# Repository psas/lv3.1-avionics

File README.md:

# lv3.1-avionics
Avionics for the LV3.1 rocket

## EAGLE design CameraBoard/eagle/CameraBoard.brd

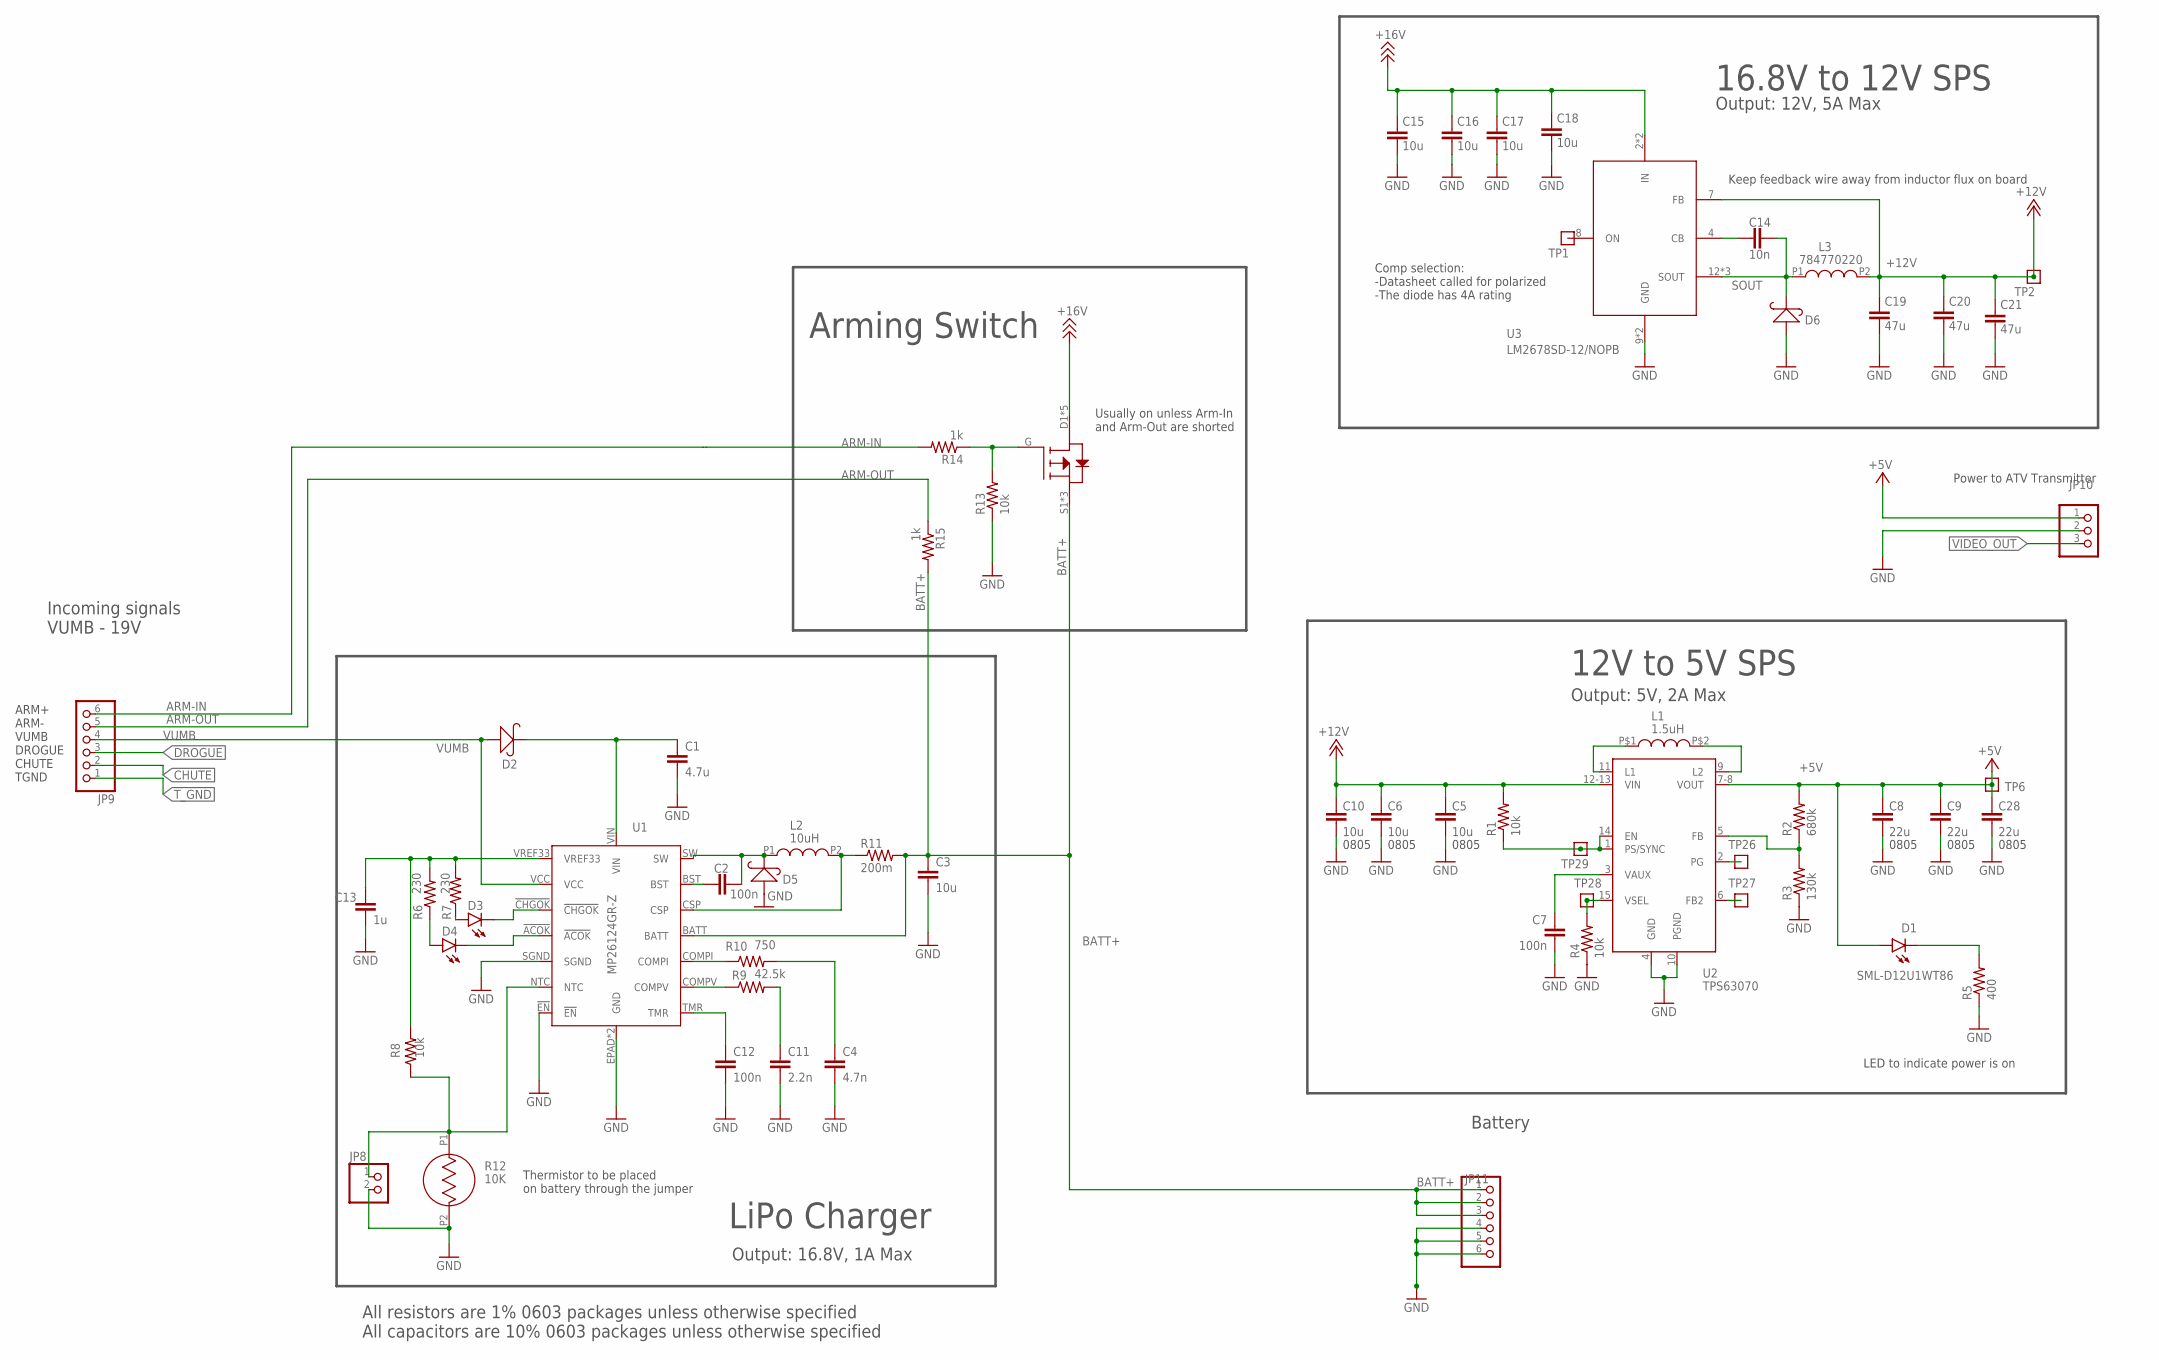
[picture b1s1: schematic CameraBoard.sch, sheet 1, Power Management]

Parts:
C1: 4.7u; .0603-A-NOSILK
C2, C12: 100n; .0603-A-NOSILK
C3: 10u; .0603-A-NOSILK
C4: 4.7n; .0603-A-NOSILK
C5: 10u; .0805-C-NOSILK; MPN CL05B104KO5NNNC
C6, C10: 10u; .0805-C-NOSILK
C7: 100n; .0603-C-NOSILK; MPN CL05B104KO5NNNC
C8: 22u; .0805-C-NOSILK; MPN CL05B104KO5NNNC
C9, C28: 22u; .0805-C-NOSILK
C11: 2.2n; .0603-A-NOSILK
C13: 1u; .0603-A-NOSILK
C14: 10n; .0603-A-NOSILK
C15, C16, C17, C18: 10u; .0805-B-NOSILK
C19, C20, C21: 47u; 1206-A
D1, D3, D4: SML-D12U1WT86; CHIPLED_0603; MPN SML-D12M1WT86
D2, D5: S2MA-13-F
D6: D_MBRS340T3G; SMC
JP8: PINHD-1X2; 1X02
JP9, JP11: PINHD-1X6; 1X06
JP10: PINHD-1X3; 1X03
L1: 1.5uH; IHLP2020CZER1R5M11
L2: 10uH; 1239AS-H-100M=P2
L3: 784770220
Q1: SI7465DP-T1-E3; SI7465DP-T1-E3CT-ND
R1, R4: 10k; .0603-C-NOSILK; MPN RC1005F6653CS
R2: 680k; .0603-C-NOSILK; MPN RC1005F6653CS
R3: 130k; .0603-C-NOSILK; MPN RC1005F6653CS
R5: 400; .0603-C-NOSILK; MPN RC1005F6653CS
R6, R7: 230; .0603-A-NOSILK
R8, R13: 10k; .0603-A-NOSILK
R9: 42.5k; .0603-A-NOSILK
R10: 750; .0603-A-NOSILK
R11: 200m; 1206-A
R12: 10K; NHQ103B375T10
R14, R15: 1k; .0603-A-NOSILK
TP1, TP2, TP6, TP26, TP27, TP28, TP29: TEST-POINT; 2MM-TEST-POINT
U1: MP26124GR-Z
U2: TPS63070; TPS63070X; MPN TPS63070RNMR
U3: LM2678SD-12/NOPB

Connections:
+5V: C8.1, C9.1, C28.1, D1.A, JP10.1, R2.2, TP6.1, U2.7-8 (VOUT); also elsewhere on the board
+12V: C5.1, C6.1, C10.1, C19.1, C20.1, C21.1, L3.P2, R1.2, TP2.1, U2.12-13 (VIN), U3.7 (FB); also elsewhere on the board
+16V: C15.1, C16.1, C17.1, C18.1, Q1.D1 (D), Q1.D2 (D), Q1.D3 (D), Q1.D4 (D), Q1.DPAD (D), U3.2 (IN), U3.3 (IN)
ARM-IN: JP9.6, R14.2
ARM-OUT: JP9.5, R15.1
BATT+: C3.1, JP11.1, JP11.2, JP11.3, Q1.S1 (S), Q1.S2 (S), Q1.S3 (S), R11.2, R15.2, U1.BATT
CHUTE: JP9.2; also elsewhere on the board
DROGUE: JP9.3; also elsewhere on the board
GND: C1.2, C3.2, C4.2, C5.2, C6.2, C7.2, C8.2, C9.2, C10.2, C11.2, C12.2, C13.2, C15.2, C16.2, C17.2, C18.2, C19.2, C20.2, C21.2, C28.2, D5.ANODE (+), D6.2 (+), JP8.2, JP10.2, JP11.4, JP11.5, JP11.6, R3.1, R4.1, R5.1, R12.P2, R13.1, U1.!EN, U1.EPAD (GND), U1.GND, U1.SGND, U2.4 (GND), U2.10 (PGND), U3.9 (GND), U3.DAP (GND); also elsewhere on the board
unnamed: D1.C, R5.2
unnamed: C1.1, D2.CATHODE (-), U1.VIN
unnamed: Q1.G, R13.2, R14.1
unnamed: C13.1, R6.2, R7.2, R8.2, U1.VREF33
unnamed: D4.A, R6.1
unnamed: D3.A, R7.1
unnamed: D3.C, U1.!CHGOK
unnamed: D4.C, U1.!ACOK
unnamed: C12.1, U1.TMR
unnamed: JP8.1, R8.1, R12.P1, U1.NTC
unnamed: R9.1, U1.COMPV
unnamed: C11.1, R9.2
unnamed: R10.1, U1.COMPI
unnamed: C4.1, R10.2
unnamed: C2.1, D5.CATHODE (-), L2.P1, U1.SW
unnamed: C2.2, U1.BST
unnamed: L2.P2, R11.1, U1.CSP
unnamed: TP1.1, U3.8 (ON)
unnamed: C14.2, U3.4 (CB)
SOUT: C14.1, D6.1 (-), L3.P1, U3.12 (SOUT), U3.13 (SOUT), U3.14 (SOUT)
TPS-EN: R1.1, TP29.1, U2.1 (PS/SYNC), U2.14 (EN)
TPS-FB: R2.1, R3.2, U2.5 (FB)
TPS-FB2: TP27.1, U2.6 (FB2)
TPS-L1: L1.P$1, U2.11 (L1)
TPS-L2: L1.P$2, U2.9 (L2)
TPS-PG: TP26.1, U2.2 (PG)
TPS-VAUX: C7.1, U2.3 (VAUX)
TPS-VSEL: R4.2, TP28.1, U2.15 (VSEL)
T_GND: JP9.1; also elsewhere on the board
VIDEO_OUT: JP10.3; also elsewhere on the board
VUMB: D2.ANODE (+), JP9.4, U1.VCC

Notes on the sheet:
Incoming signals VUMB - 19V
Battery
0805
LED to indicate power is on
ARM+ ARM- VUMB DROGUE CHUTE TGND
Usually on unless Arm-In and Arm-Out are shorted
12V to 5V SPS
LiPo Charger
16.8V to 12V SPS
Arming Switch
Power to ATV Transmitter
Keep feedback wire away from inductor flux on board
Comp selection: -Datasheet called for polarized -The diode has 4A rating
Thermistor to be placed on battery through the jumper
All resistors are 1% 0603 packages unless otherwise specified All capacitors are 10% 0603 packages unless otherwise specified
Output: 12V, 5A Max
Output: 5V, 2A Max
Output: 16.8V, 1A Max

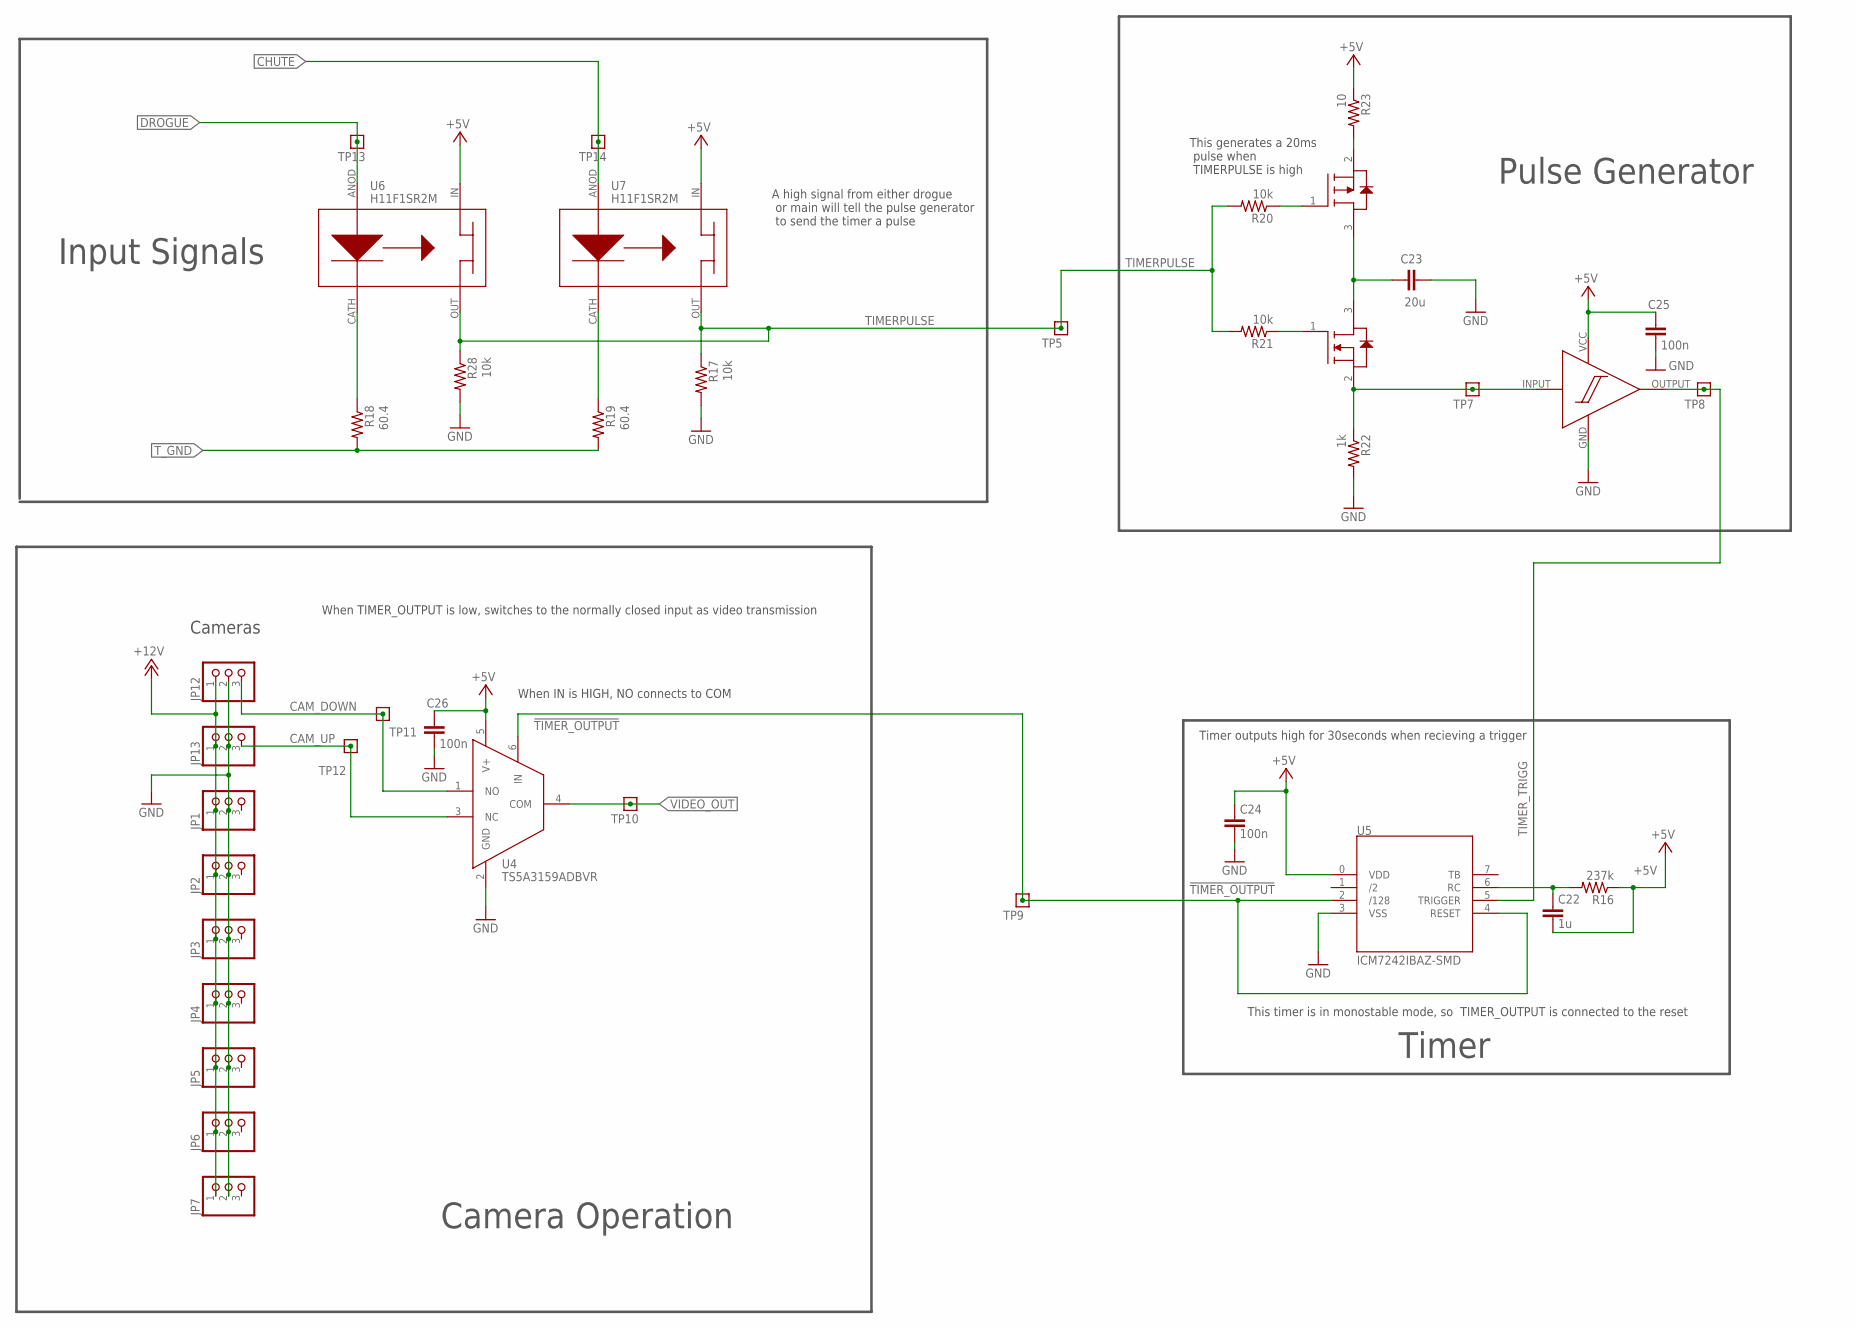
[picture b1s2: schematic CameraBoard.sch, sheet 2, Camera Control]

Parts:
C22: 1u; .0603-C-NOSILK
C23: 20u; .0603-C-NOSILK
C24, C25, C26: 100n; .0603-C-NOSILK
JP1, JP2, JP3, JP4, JP5, JP6, JP7, JP12, JP13: PINHD-1X3; 1X03
Q2: BVSS123LT1G
Q3: BSS84
R16: 237k; .0603-A-NOSILK
R17, R28: 10k; .0603-C-NOSILK
R18, R19: 60.4; .0603-C-NOSILK
R20, R21: 10k; .0603-A-NOSILK
R22: 1k; .0603-A-NOSILK
R23: 10; .0805-A-NOSILK
TP5, TP7, TP8, TP9, TP10, TP11, TP12, TP13, TP14: TEST-POINT; 2MM-TEST-POINT
U4: TS5A3159ADBVR
U5: ICM7242IBAZ-SMD
U6, U7: H11F1SR2M; MPN H11F1SR2M
U8: SN74LVC1G17DCKR

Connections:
!TIMER_OUTPUT: TP9.1, U4.6 (IN), U5.2 (/128), U5.4 (RESET)
+5V: C22.2, C24.1, C25.2, C26.2, R16.1, R23.1, U4.5 (V+), U5.0 (VDD), U6.IN, U7.IN, U8.VCC; also elsewhere on the board
+12V: JP1.1, JP2.1, JP3.1, JP4.1, JP5.1, JP6.1, JP7.1, JP12.1, JP13.1; also elsewhere on the board
CAM_DOWN: JP12.3, TP11.1, U4.1 (NO)
CAM_UP: JP13.3, TP12.1, U4.3 (NC)
CHUTE: TP14.1, U7.ANOD; also elsewhere on the board
DROGUE: TP13.1, U6.ANOD; also elsewhere on the board
GND: C23.2, C24.2, C25.1, C26.1, JP1.2, JP2.2, JP3.2, JP4.2, JP5.2, JP6.2, JP7.2, JP12.2, JP13.2, R17.2, R22.2, R28.2, U4.2 (GND), U5.3 (VSS), U8.GND; also elsewhere on the board
unnamed: R18.1, U6.CATH (CAT)
unnamed: R19.1, U7.CATH (CAT)
unnamed: C22.1, R16.2, U5.6 (RC)
unnamed: C23.1, Q2.3 (D), Q3.3 (D)
unnamed: Q3.2 (S), R23.2
unnamed: Q3.1 (G), R20.1
unnamed: Q2.1 (G), R21.1
SCHMITTIN: Q2.2 (S), R22.1, TP7.1, U8.INPUT (A)
TIMERPULSE: R17.1, R20.2, R21.2, R28.1, TP5.1, U6.OUT, U7.OUT
TIMER_TRIGG: TP8.1, U5.5 (TRIGGER), U8.OUTPUT (Y)
T_GND: R18.2, R19.2; also elsewhere on the board
VIDEO_OUT: TP10.1, U4.4 (COM); also elsewhere on the board

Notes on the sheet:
Cameras
Camera Operation
This timer is in monostable mode, so TIMER_OUTPUT is connected to the reset
A high signal from either drogue or main will tell the pulse generator to send the timer a pulse
Input Signals
Timer
Pulse Generator
This generates a 20ms pulse when TIMERPULSE is high
When TIMER_OUTPUT is low, switches to the normally closed input as video transmission
When IN is HIGH, NO connects to COM
Timer outputs high for 30seconds when recieving a trigger

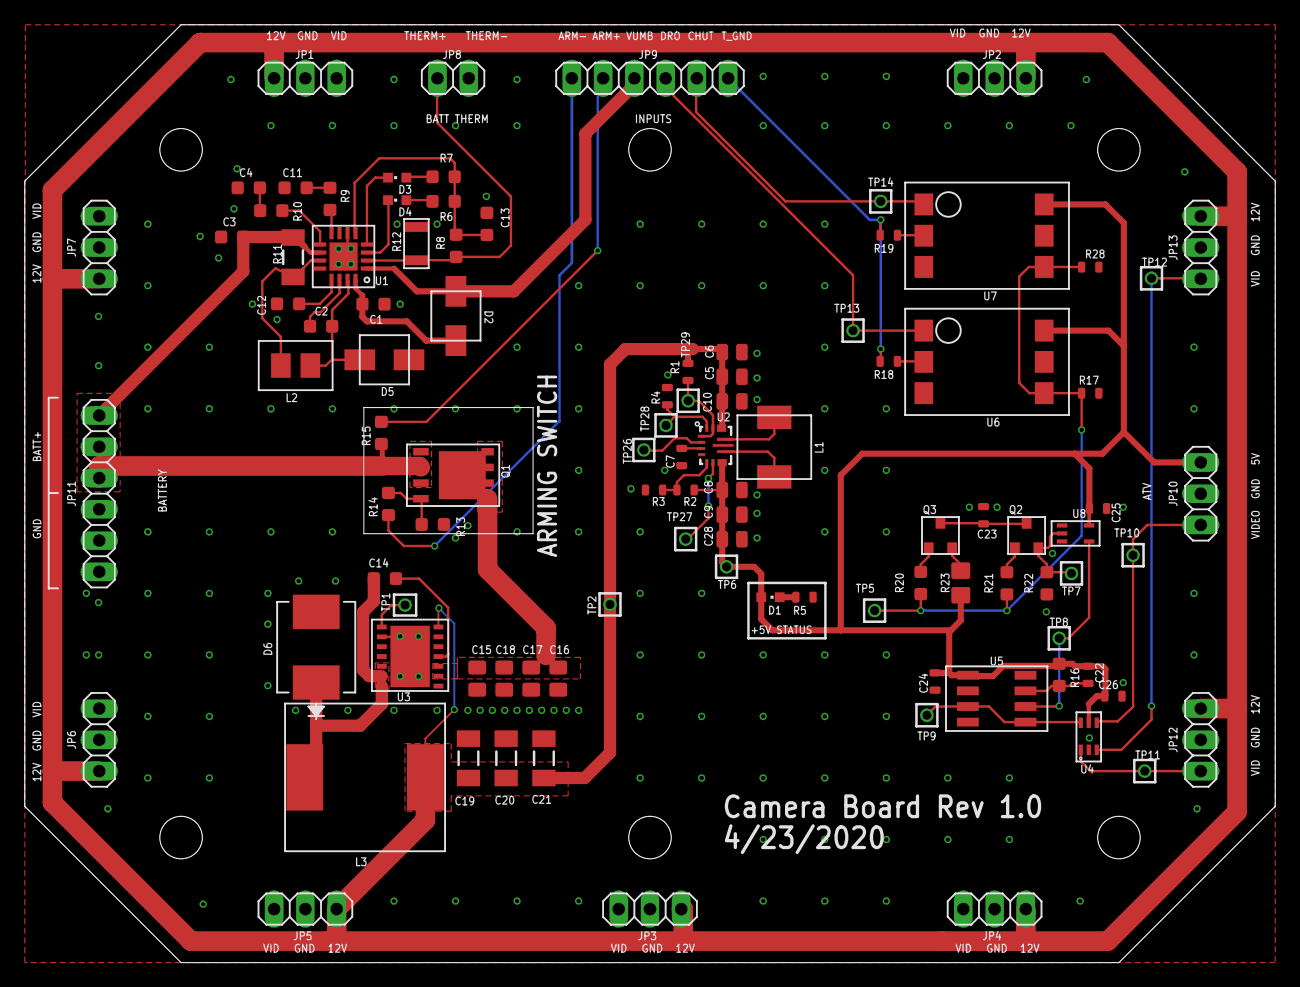
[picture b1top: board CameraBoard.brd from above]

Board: 2 copper layers, 101.6 x 76.2 mm, 100 parts (0 on the bottom side), 53 nets.

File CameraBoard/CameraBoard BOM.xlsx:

Qty | Parts | MAN | MPN | Description | DIS | DPN
1 | JP8 | TBD | TBD | 2 PIN HEADER | TBD | TBD
1 | L1 | Vishay Dale | IHLP2020BZER4R7M11 | 4.7µH Shielded Molded Inductor 3.2A 81.3mOhm Max Nonstandard | Digi-Key | 541-1222-1-ND
1 | R23 | Yageo | RC0805FR-0710RL | 10 Ohms ±1% 0.125W, 1/8W Chip Resistor 0805 (2012 Metric) Moisture Resistant Th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 | Digi-Key | 311-10.0CRCT-ND
1 | R12 | Amphenol Advanced Sensors | NHQ103B375T10 | NTC Thermistor 10k 1206 (3216 Metric) | Digi-Key | 235-1109-1-ND
1 | C14 | KEMET | C0603C103M5RACTU | 10000pF ±20% 50V Ceramic Capacitor X7R 0603 (1608 Metric) | Digi-Key | 399-7842-1-ND
1 | L2 | Murata Electronics | 1239AS-H-100M=P2 | 10µH Shielded Wirewound Inductor 1A 460mOhm Max 1008 (2520 Metric) | Digi-Key | 490-10563-2-ND
1 | R3 | Yageo | RC0805JR-07130KL | 130 kOhms ±5% 0.125W, 1/8W Chip Resistor 0805 (2012 Metric) Moisture Resistant 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 | Digi-Key | 311-130KARCT-ND
1 | C11 | KEMET | C0603C222K5RACTU | 2200pF ±10% 50V Ceramic Capacitor X7R 0603 (1608 Metric) | Digi-Key | NTC Thermistor 10k 1206 (3216 Metric)
1 | R11 | Vishay Dale | RCWE0603R200FKEA | 200 mOhms ±1% 0.2W, 1/5W Chip Resistor 0603 (1608 Metric) Automotive AEC-Q200, 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 | Digi-Key | RCWE.2CCT-ND
1 | R16 | Yageo | RC0603FR-07237KL | 237 kOhms ±1% 0.1W, 1/10W Chip Resistor 0603 (1608 Metric) Moisture Resistant T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 | Digi-Key | 311-237KHRCT-ND
1 | C4 | KEMET | C0603C472J5RACTU | 4700pF ±5% 50V Ceramic Capacitor X7R 0603 (1608 Metric) | Digi-Key | 399-1088-1-ND
1 | C1 | KEMET | C0603C475K9PACTU | 4.7µF ±10% 6.3V Ceramic Capacitor X5R 0603 (1608 Metric) | Digi-Key | 399-3482-1-ND
1 | R5 | Yageo | RT0805BRD07402RL | 402 Ohms ±0.1% 0.125W, 1/8W Chip Resistor 0805 (2012 Metric) Thin Film | Digi-Key | YAG4897CT-ND
1 | R9 | Panasonic Electronic Components | ERJ-1GNF4302C | 43 kOhms ±1% 0.05W, 1/20W Chip Resistor 0201 (0603 Metric) Automotive AEC-Q200 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 | Digi-Key | P122417CT-ND
1 | R2 | Yageo | RC0603FR-07680KL | 680 kOhms ±1% 0.1W, 1/10W Chip Resistor 0603 (1608 Metric) Moisture Resistant T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 | Digi-Key | 311-680KHRCT-ND
1 | R10 | Rohm Semiconductor | ESR03EZPJ751 | 750 Ohms ±5% 0.25W, 1/4W Chip Resistor 0603 (1608 Metric) Automotive AEC-Q200, 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 | Digi-Key | RHM750DCT-ND
1 | L3 | Würth Elektronik | 784770220 | 22µH Shielded Wirewound Inductor 4A 44.5mOhm Max Nonstandard | Digi-Key | 732-6785-1-ND
1 | Q3 | ON Semiconductor | BSS84 | P-Channel 50V 130mA (Ta) 360mW (Ta) Surface Mount SOT-23-3 | Digi-Key | BSS84CT-ND
1 | Q2 | ON Semiconductor | BVSS123LT1G | N-Channel 100V 170mA (Ta) 225mW (Ta) Surface Mount SOT-23-3 | Digi-Key | BVSS123LT1GOSCT-ND
1 | D6 | ON Semiconductor |  | Diode Schottky 40V 4A Surface Mount SMC | Digi-Key | MBRS340T3GOSTR-ND
1 | U5 | Intersil | ICM7242IBAZ | Counter/Timer Circuit (CTC), Binary IC 0.1Hz ~ 13MHz 8-SOIC | Digi-Key | 2156-ICM7242IBAZ-I
1 | U3 | Texas Instruments | LM2678SD-12/NOPB | Buck Switching Regulator IC Positive Fixed 12V 1 Output 5A 14-VDFN Exposed Pad | Digi-Key | 296-40166-1-ND
1 | U1 | Monolithic Power Systems Inc. | MP26124GR-Z | Charger IC Lithium-Ion 16-QFN (4x4) | Digi-Key | 1589-1993-1-ND
1 | Q1 | Vishay Siliconix | nix SI7465DP-T1-E3 | P-Channel 60V 3.2A (Ta) 1.5W (Ta) Surface Mount PowerPAK® SO-8 | DigiKey | SI7465DP-T1-E3CT-ND
1 | U8 | Texas Instruments | SN74LVC1G17DCKR | Buffer, Non-Inverting 1 Element 1 Bit per Element Push-Pull Output SC-70-5 | Digi-Key | 296-11934-1-ND
1 | U2 | Texas Instruments | TPS63070RNMR | Buck-Boost Switching Regulator IC Positive Adjustable 2.5V 1 Output 3.6A (Switc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 | Digi-Key | 296-44874-2-ND
1 | U4 | Texas Instruments | TS5A3159ADBVR | 1 Circuit IC Switch 2:1 900mOhm SOT-23-6 | Digi-Key | 296-19265-2-ND
1 | C23 | Yageo | CC0603MRX5R5BB226 | 22µF ±20% 6.3V Ceramic Capacitor X5R 0603 (1608 Metric) | Digi-Key | 311-1815-1-ND
1 | C3 | Yageo | CC0603KRX5R5BB106 | 10µF ±10% 6.3V Ceramic Capacitor X5R 0603 (1608 Metric) | Digi-Key | 311-1781-1-ND
2 | C13, C22 | KEMET | C0603C105K8PACTU | 1µF ±10% 10V Ceramic Capacitor X5R 0603 (1608 Metric) | Digi-Key | 399-3118-1-ND
2 | JP9, JP11 |  |  | 6 PIN HEADER | Digi-Key
2 | R6, R7 | Yageo | RC0603FR-07232RL | 232 Ohms ±1% 0.1W, 1/10W Chip Resistor 0603 (1608 Metric) Moisture Resistant Th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 | Digi-Key | 311-232HRCT-ND
2 | R18, R19 | Yageo | RC0603FR-0760R4L | 60.4 Ohms ±1% 0.1W, 1/10W Chip Resistor 0603 (1608 Metric) Moisture Resistant T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 | Digi-Key | 311-60.4HRCT-ND
2 | U6, U7 | ON Semiconductor | H11F1SR2M | Optoisolator MOSFET Output 7500Vpk 1 Channel 6-SMD | Digi-Key | H11F1SR2MCT-ND
2 | D2, D5 | Diodes Incorporated | S2MA-13-F | Diode Standard 1000V 1.5A Surface Mount SMA | Digi-Key | S2MA-FDICT-ND
3 | R14, R15, R22 | Yageo | RC0603JR-071KL | 1 kOhms ±5% 0.1W, 1/10W Chip Resistor 0603 (1608 Metric) Moisture Resistant Thi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 | Digi-Key | 311-1.0KGRCT-ND
3 | C19, C20, C21 | Murata Electronics | GRM31CR61A476KE15L | 47µF ±10% 10V Ceramic Capacitor X5R 1206 (3216 Metric) | Digi-Key | 490-9673-1-ND
3 | D1, D3, D4 | Rohm Semiconductor | SML-D12M1WT86 | LED | Digi-Key | SML-D12M1WT86CT-ND
3 | C8, C9, C28 | KEMET | C0805C226K9PAC7800 | 22µF ±10% 6.3V Ceramic Capacitor X5R 0805 (2012 Metric) | Digi-Key | 399-11661-1-ND
6 | C2, C7, C12, C24, C25, C26 | KEMET | C0603C104Z3VACTU | 0.1µF -20%, +80% 25V Ceramic Capacitor Y5V (F) 0603 (1608 Metric) | Digi-Key | 399-1100-1-ND
7 | C6, C5, C10, C15, C16, C17, C18 | KEMET | C0805C106K9PACTU | 10µF ±10% 6.3V Ceramic Capacitor X5R 0805 (2012 Metric) | Digi-Key | 399-3138-1-ND
8 | R17, R28, R1, R4, R8, R13, R20, R21 | Yageo | RC0603FR-0710KL | 10 kOhms ±1% 0.1W, 1/10W Chip Resistor 0603 (1608 Metric) Moisture Resistant Th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 | Digi-Key | 311-10.0KHRCT-ND
10 | JP1, JP2, JP3, JP4, JP5, JP6, JP7, JP10, JP12, JP13 |  |  | 3 PIN HEADER | Digi-Key

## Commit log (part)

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2020-02-05 added file
2020-04-22 adding first design review notes
2020-04-23 power schematic for board
2020-04-23 first draft of schematic complete
2020-04-24 layed out board before routing
2020-04-24 finished board layout before routing
2020-04-24 completed routing of board rev 1.0
2020-04-28 new image
2020-04-29 added all the suggestions from first design review
2020-04-29 moved text around, and added new .jpg
2020-07-07 added BOM
2020-07-20 Minor erc and drc cleanup, ground plane cleanup, nothing major.
2020-10-05 Added molex connectors
2023-08-20 Added KiCAD 7 import of CameraBoard. Updated .gitignore file, too.
2025-06-24 Updated KiCAD EAGLE import to latest KiCAD 9.0.2.
2025-07-02 Added wiring diagram; avionics module complete!
2025-07-02 Added connector notes
2025-07-02 Add note on extra wire length
2025-07-16 Added umbilical ring connections
2025-07-16 Minor polishing
2025-07-30 Added another connector on umbilical cord
2025-08-02 Changed pulldown to 150k and added note about flipped connector.
2025-08-03 Cleaned up second page - fixed optoisolator symbols, added notes about levels and times, and cleaned up alot. Put in notes about mod wires.
2025-08-04 Make schematic better, mostly cleaning up EAGLE import errors
2026-01-28 Added umbilical cable adapter with labels
2026-03-12 Minor updates to PCB
2026-04-26 replaced the timer logic for a d flip flop
